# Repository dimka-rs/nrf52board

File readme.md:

# NRF52 + LoRa dev board

## Known issues
- Q1 footprint does not match any fets I have

## Components
- [NRF52 module E73-2G4M04S](https://www.aliexpress.com/item/32820692238.html) 
- [LoRa module RFM95W](https://www.aliexpress.com/item/32811523237.html)
- USB-UART CP2102
- LDO LP5907MFX-3.3
- LiPo charger MCP73831-2-OT

[See board pinout](pinout.md)

Board images:

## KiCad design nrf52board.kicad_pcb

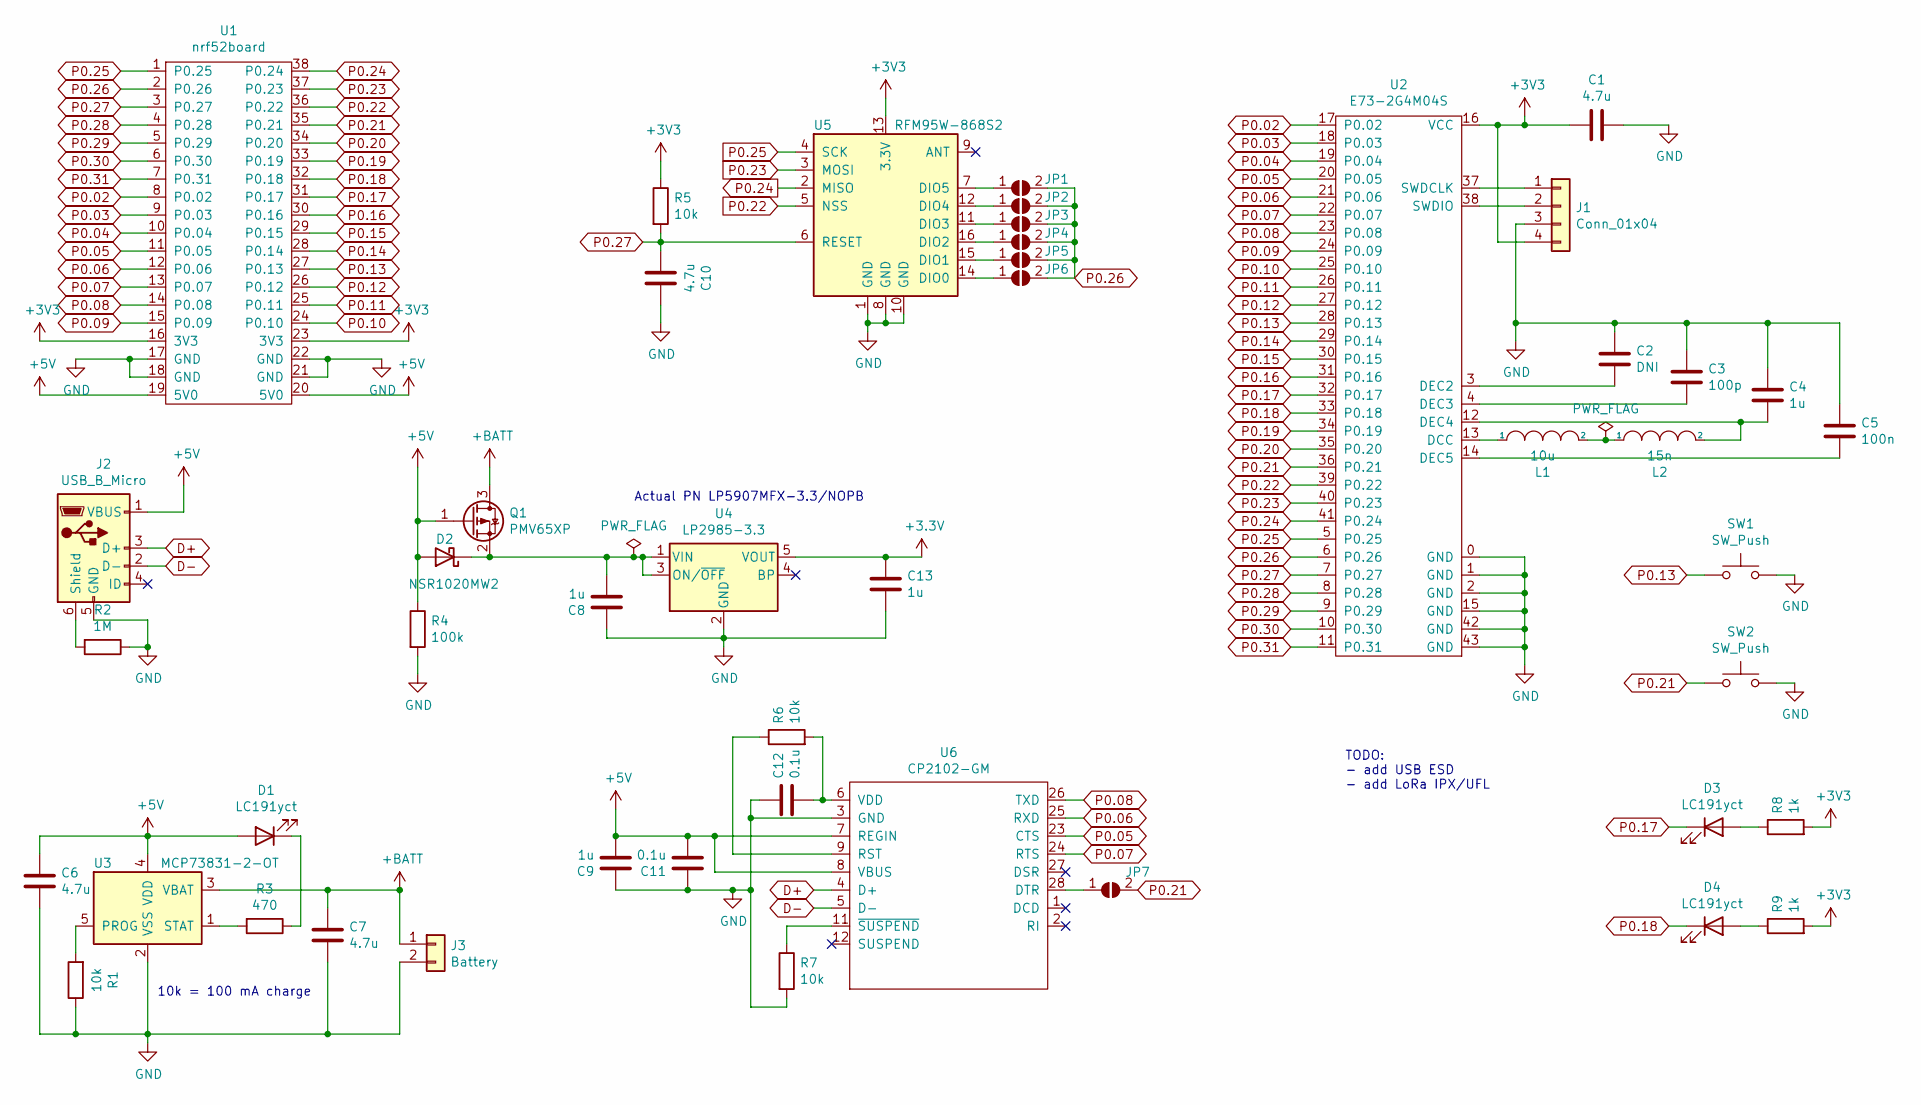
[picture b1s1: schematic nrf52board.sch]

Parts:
C1, C6, C7, C10: 4.7u; C_0603_1608Metric
C2: DNI; C_0603_1608Metric
C3: 100p; C_0603_1608Metric
C4, C8, C9, C13: 1u; C_0603_1608Metric
C5: 100n; C_0603_1608Metric
C11, C12: 0.1u; C_0603_1608Metric
D1, D3, D4: LC191yct; LED_0603_1608Metric
D2: NSR1020MW2; D_SOD-323
J1: Conn_01x04; PinHeader_1x04_P2.54mm_Vertical
J2: USB_B_Micro; USB_Micro-B_Amphenol_10103594-0001LF_Horizontal
J3: Battery; PinHeader_1x02_P2.54mm_Vertical
JP1, JP2, JP3, JP4, JP5, JP6, JP7: SolderJumper_2_Open; SolderJumper-2_P1.3mm_Open_RoundedPad1.0x1.5mm
L1: 10u; L_0805_2012Metric
L2: 15n; L_0805_2012Metric
Q1: PMV65XP; SOT-23
R1, R5, R6, R7: 10k; R_0603_1608Metric
R2: 1M; R_0603_1608Metric
R3: 470; R_0603_1608Metric
R4: 100k; R_0603_1608Metric
R8, R9: 1k; R_0603_1608Metric
SW1, SW2: SW_Push; Panasonic_EVQPUJ_EVQPUA
U1: nrf52board
U2: E73-2G4M04S
U3: MCP73831-2-OT; SOT-23-5
U4: LP2985-3.3; SOT-23-5
U5: RFM95W-868S2; Hopref_RFM9XW_SMD
U6: CP2102-GM; QFN-28-1EP_5x5mm_P0.5mm_EP3.35x3.35mm

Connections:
+5V: C6.1, C9.2, C11.2, D1.2 (A), D2.2 (A), J2.1 (VBUS), Q1.1 (G), R4.1, U1.19 (5V0), U1.20 (5V0), U3.4 (VDD), U6.7 (REGIN), U6.8 (VBUS)
+BATT: C7.1, J3.1, Q1.3 (D), U3.3 (VBAT)
D+: J2.3 (D+), U6.4 (D+)
D-: J2.2 (D-), U6.5 (D-)
GND: C1.1, C2.2, C3.2, C4.2, C5.2, C6.2, C7.2, C8.1, C9.1, C10.1, C11.1, C12.1, C13.2, J1.3, J2.5 (GND), J3.2, R1.1, R2.1, R4.2, R7.2, SW1.2, SW2.2, U1.17 (GND), U1.18 (GND), U1.21 (GND), U1.22 (GND), U2.0 (GND), U2.1 (GND), U2.2 (GND), U2.15 (GND), U2.42 (GND), U2.43 (GND), U3.2 (VSS), U4.2 (GND), U5.1 (GND), U5.8 (GND), U5.10 (GND), U6.3 (GND)
unnamed: C2.1, U2.3 (DEC2)
unnamed: C3.1, U2.4 (DEC3)
unnamed: C4.1, L2.2, U2.12 (DEC4)
unnamed: C5.1, U2.14 (DEC5)
unnamed: C8.2, D2.1 (K), Q1.2 (S), U4.1 (VIN), U4.3 (ON/~OFF~)
unnamed: C12.2, R6.2, U6.6 (VDD)
unnamed: D1.1 (K), R3.1
unnamed: D3.2 (A), R8.1
unnamed: D4.2 (A), R9.1
unnamed: J1.1, U2.37 (SWDCLK)
unnamed: J1.2, U2.38 (SWDIO)
unnamed: J2.6 (Shield), R2.2
unnamed: JP1.1 (A), U5.7 (DIO5)
unnamed: JP2.1 (A), U5.12 (DIO4)
unnamed: JP3.1 (A), U5.11 (DIO3)
unnamed: JP4.1 (A), U5.16 (DIO2)
unnamed: JP5.1 (A), U5.15 (DIO1)
unnamed: JP6.1 (A), U5.14 (DIO0)
unnamed: JP7.1 (A), U6.28 (DTR)
unnamed: L1.1, U2.13 (DCC)
unnamed: L1.2, L2.1
unnamed: R1.2, U3.5 (PROG)
unnamed: R3.2, U3.1 (STAT)
unnamed: R6.1, U6.9 (RST)
unnamed: R7.1, U6.11 (~SUSPEND)
P0.02: U1.8 (P0.02), U2.17 (P0.02)
P0.03: U1.9 (P0.03), U2.18 (P0.03)
P0.04: U1.10 (P0.04), U2.19 (P0.04)
P0.05: U1.11 (P0.05), U2.20 (P0.05), U6.23 (CTS)
P0.06: U1.12 (P0.06), U2.21 (P0.06), U6.25 (RXD)
P0.07: U1.13 (P0.07), U2.22 (P0.07), U6.24 (RTS)
P0.08: U1.14 (P0.08), U2.23 (P0.08), U6.26 (TXD)
P0.09: U1.15 (P0.09), U2.24 (P0.09)
P0.10: U1.24 (P0.10), U2.25 (P0.10)
P0.11: U1.25 (P0.11), U2.26 (P0.11)
P0.12: U1.26 (P0.12), U2.27 (P0.12)
P0.13: SW1.1, U1.27 (P0.13), U2.28 (P0.13)
P0.14: U1.28 (P0.14), U2.29 (P0.14)
P0.15: U1.29 (P0.15), U2.30 (P0.15)
P0.16: U1.30 (P0.16), U2.31 (P0.16)
P0.17: D3.1 (K), U1.31 (P0.17), U2.32 (P0.17)
P0.18: D4.1 (K), U1.32 (P0.18), U2.33 (P0.18)
P0.19: U1.33 (P0.19), U2.34 (P0.19)
P0.20: U1.34 (P0.20), U2.35 (P0.20)
P0.21: JP7.2 (B), SW2.1, U1.35 (P0.21), U2.36 (P0.21)
P0.22: U1.36 (P0.22), U2.39 (P0.22), U5.5 (NSS)
P0.23: U1.37 (P0.23), U2.40 (P0.23), U5.3 (MOSI)
P0.24: U1.38 (P0.24), U2.41 (P0.24), U5.2 (MISO)
P0.25: U1.1 (P0.25), U2.5 (P0.25), U5.4 (SCK)
P0.26: JP1.2 (B), JP2.2 (B), JP3.2 (B), JP4.2 (B), JP5.2 (B), JP6.2 (B), U1.2 (P0.26), U2.6 (P0.26)
P0.27: C10.2, R5.2, U1.3 (P0.27), U2.7 (P0.27), U5.6 (RESET)
P0.28: U1.4 (P0.28), U2.8 (P0.28)
P0.29: U1.5 (P0.29), U2.9 (P0.29)
P0.30: U1.6 (P0.30), U2.10 (P0.30)
P0.31: U1.7 (P0.31), U2.11 (P0.31)

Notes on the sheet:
Actual PN LP5907MFX-3.3/NOPB
TODO: - add USB ESD - add LoRa IPX/UFL
10k = 100 mA charge

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
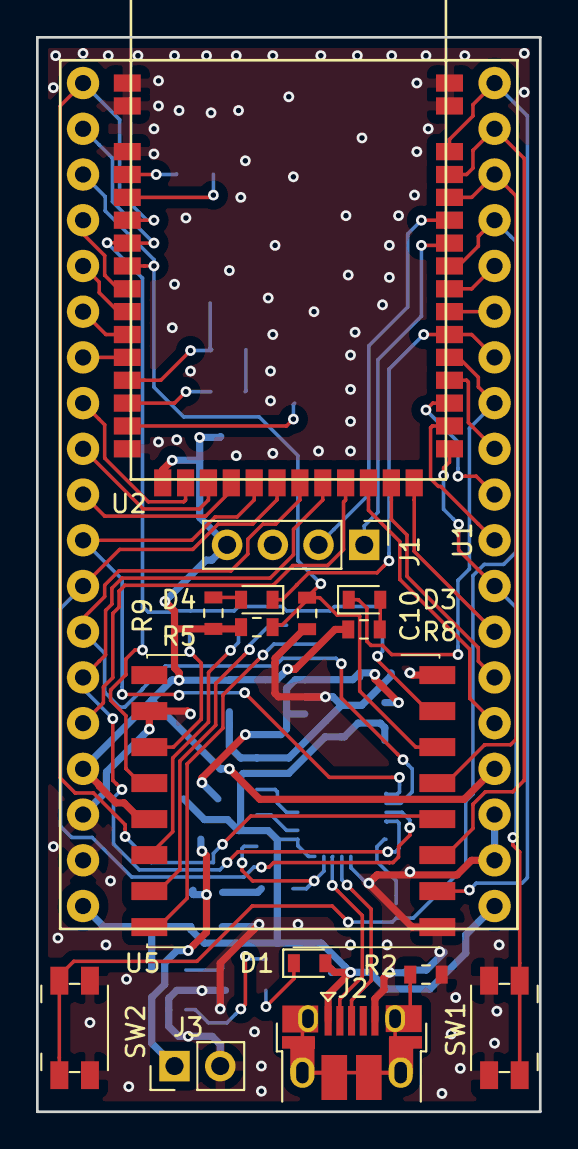
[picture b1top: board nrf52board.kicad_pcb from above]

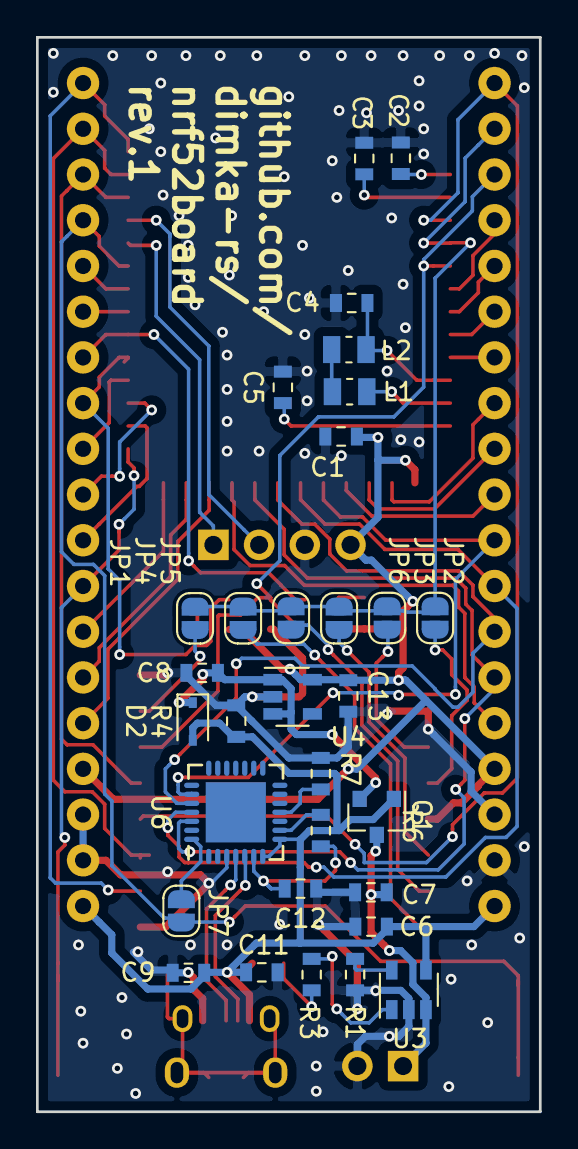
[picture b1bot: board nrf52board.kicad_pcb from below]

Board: 2 copper layers, 27.9 x 59.7 mm, 47 parts (31 on the bottom side), 61 nets.

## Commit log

2018-03-10 added board symbol
2018-03-10 added simple pcb
2018-03-25 updated module foorptint
2018-04-01 moved libs to kicad-libs
2018-04-02 sch: added power
2018-04-08 charger done
2018-04-09 sch: update todo
2018-04-12 sch: updated TODO
2018-04-14 sch: added cp2102, lora connected
2018-04-17 sch: added one more btn and led
2018-04-17 pcb: half way through
2018-04-20 pcb: almost done
2018-04-20 pcb: traciong done
2018-04-20 pcb: done
2018-04-24 gerbers created
2018-04-26 gerbers created fix
2018-11-20 add pinout img
2019-04-27 add pinout
2019-04-27 rescue
2019-07-20 update docs and images
2019-07-22 add interactive bom
2019-07-22 add assembled board image
2019-07-26 readme: todo moved to wiki
2019-07-26 pinout: add alt functions
2019-07-26 sch: rescue
2021-03-08 Change Q1 to PMV65XP
2021-03-08 Update Q1 on PCB
2021-05-23 Fix BOM
2021-05-26 add button name
